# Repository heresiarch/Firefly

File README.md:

# Firefly
Own Dervivation of an electronic Firefly simulator with AVR Tiny based on a thread from http://www.mikrocontroller.net/topic/99803.  
This device is really nice to see and a perfect gift.  
I use Eclipse Kepler with avrdude and AVR Eclipse Plugin http://sourceforge.net/projects/avr-eclipse/
PCB Layout with Eagle is included.  
Variant 1 was not running stable after a couple of weeks.  
Variant 2 got an hardware watchdog circuit applied was running longer but also died after couple of months.  
Some people in the forum have the circuit running for years, but I could not dig out why mine was failing.  
The circuit will be powerd with an solar cell and 2 AAA NiMH akkus, and will dimm the leds like fireflies in darkness using different patterns.  
The original author of the SW is mentioned in the thread above.   
I will make a new PCB with gold plated battery clips, which is in my opinion the problem of the unstability.
Also I'm thinking of converting the project to an PIC24 using only C and get rid of the assembler stuff.

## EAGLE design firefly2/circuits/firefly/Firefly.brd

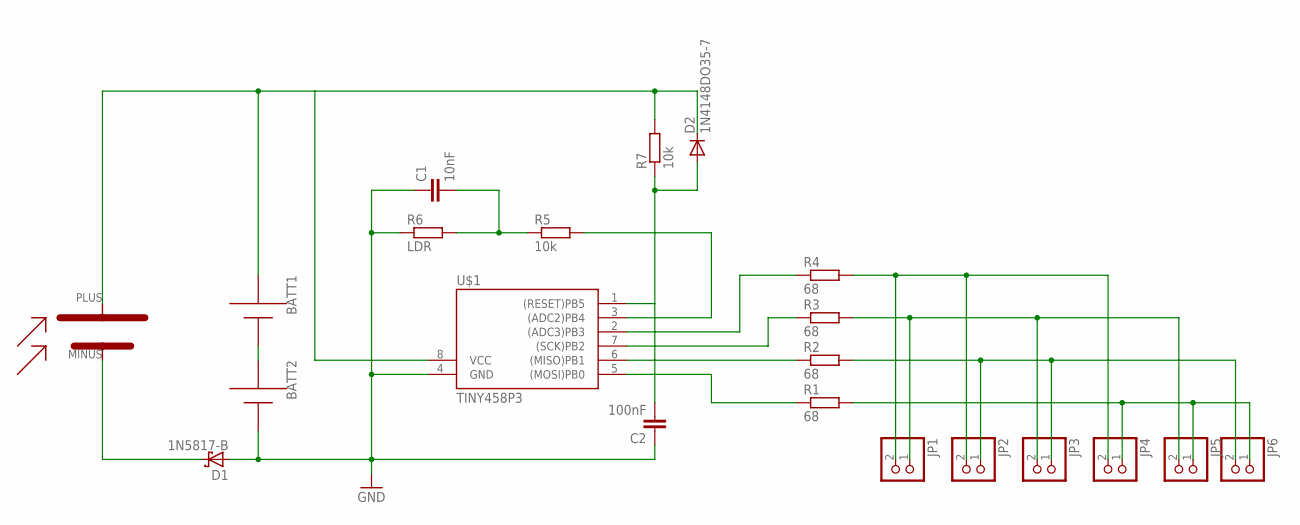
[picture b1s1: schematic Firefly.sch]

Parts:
BATT1, BATT2: AAA; 12BH412
C1: 10nF; C025-025X050
C2: 100nF; C075-032X103
D1: 1N5817-B; DO41-7.6
D2: 1N4148DO35-7; DO35-7
JP1, JP2, JP3, JP4, JP5, JP6: PINHD-1X2; 1X02
R1, R2, R3, R4: 68; 0204/7
R5: 10k; 0207/10
R6: LDR; 0204/7
R7: 10k; 0204/7
U$1: TINY458P3; DIL08
U$2: SOLARCELL4V35MACONRAD; SOLARCELL35X39

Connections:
GND: BATT2.-, C1.1, C2.1, D1.A, R6.1, U$1.4 (GND)
unnamed: R1.1, U$1.5 ((MOSI)PB0)
unnamed: R2.1, U$1.6 ((MISO)PB1)
unnamed: R3.1, U$1.7 ((SCK)PB2)
unnamed: R4.1, U$1.2 ((ADC3)PB3)
unnamed: JP1.2, JP2.2, JP4.2, R4.2
unnamed: BATT1.-, BATT2.+
unnamed: JP2.1, JP3.1, JP6.2, R2.2
unnamed: JP1.1, JP3.2, JP5.2, R3.2
unnamed: C2.2, D2.A, R7.1, U$1.1 ((RESET)PB5)
unnamed: JP4.1, JP5.1, JP6.1, R1.2
unnamed: BATT1.+, D2.C, R7.2, U$1.8 (VCC), U$2.PLUS
unnamed: D1.C, U$2.MINUS
unnamed: R5.2, U$1.3 ((ADC2)PB4)
unnamed: C1.2, R5.1, R6.2

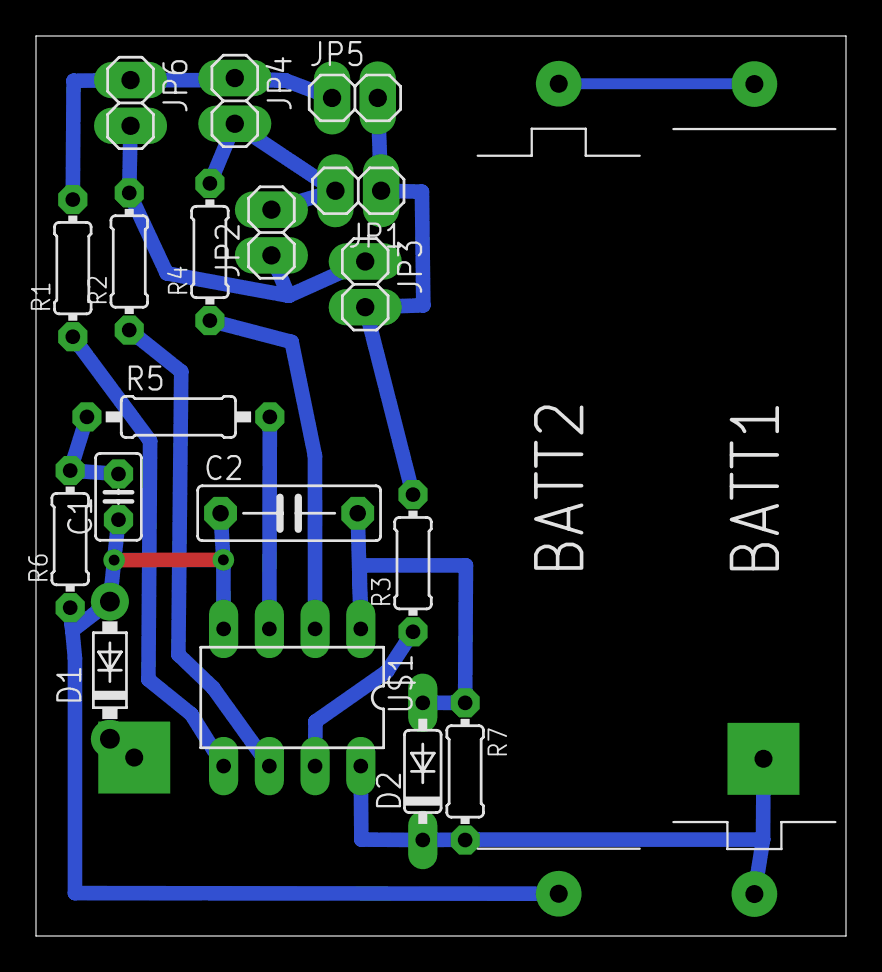
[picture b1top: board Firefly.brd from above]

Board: 2 copper layers, 45.0 x 50.0 mm, 21 parts (1 on the bottom side), 15 nets.

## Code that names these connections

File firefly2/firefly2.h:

#ifndef FIREFLY_H
#define FIREFLY_H

#include <inttypes.h>
#include <avr/eeprom.h>
#include <avr/pgmspace.h>
#include <util/delay.h>
#include "lfsr32.h"
#include "wave.h"

/*
   PB2 =      = InOut = LED0
   PB1 =      = InOut = LED1
   PB0 =      = InOut = LED2
   PB5 =      = InOut = LED3
   PB3 = ADC3 = Input = BAT+/SOLAR+
   PB4 = ADC2 = Input = SOLAR-

   connection schemata for LEDs are:
   - two antiparallel connected LEDs to two wire, makes six such wires
   - connect these wires to PB0-PB1, PB0-PB2, PB0-PB5, PB1-PB2, PB1-PB5, PB2-PB5
   - the order of these connections are not relevant

   setup:
   - install AVRootloader.HEX on AVR
   - setup fuses to XTAL=8Mhz, no Brownout Detection, no WDTON
   - connect RS232 on PB2 and test Bootloader (reading/writing EEPROM)
   - setup fuses to disable RESET Pin and lockbits
   - connect with bootloader an program FireFly.HEX
*/


#define FLAG_WAVE           (1 << 0)                    // PWM is active for a LED
#define FLAG_TIMER          (1 << 1)                    // PWM is active
#define FLAG_UPDATE         (1 << 2)                    // Watchdog signaled a update
#define FLAG_ISNIGHT        (1 << 3)                    // is at night
#define FLAG_MEASURE        (1 << 4)                    // measure battery and solarpanel

//#define MEASURE_INTERVAL    (uint16_t)(6 *  3750)       // each 6 minutes measure interval
//#define MEASURE_INTERVAL    (uint16_t)(2 *  3750)       // each 2 minutes measure interval
#define MEASURE_INTERVAL    (uint16_t)(1 *  375)       // each 2 * 6 seconds measure interval

#define BATTERY_OK          (uint16_t)(0.9 * 400)       // 0.9 Volt

// LED Rows, Pins connected to LEDs
#define R0  (1 << PB0)
#define R1  (1 << PB1)
#define R2  (1 << PB2)
#define R3  (1 << PB3)

// bitmasks for driving LEDs on PORTB and DDRB, first value are for PORTB (always 1),
// next 3 values for DDRB to connect LEDs to GND (on) or as high-Z input (off)
// you can reorder this array iff needed so long as each row depends to only one PORTB value,
// means in each row you can savely reorder the colums and/or you can savely reorder the rows.
const prog_uint8_t ddr_data[16] = {
    R0, R0^R1, R0^R2, R0^R3,
    R1, R1^R0, R1^R2, R1^R3,
    R2, R2^R0, R2^R1, R2^R3,
    R3, R3^R0, R3^R1, R3^R2};

// a Firefly
typedef struct {
    uint16_t wave_end;                              // pointer to end of wave samples
    uint16_t wave_ptr;                              // pointer to current wave sample == PWM Dutycylce of one LED
    uint16_t hungry;                                // energy points that must be feed to activate lightning of firefly
    uint16_t energy;                                // next energy points to add to hungry
} firefly_t;                                        // one energy/hungry point relates to one WDT cycle of 16ms

typedef firefly_t* firefly_p;

// some macros, don't use WinAVR GCC default macros because these produce inefficient compiled code
#define  wdt_reset()         asm volatile("wdr")
#define  cli()               asm volatile("cli")
#define  sei()               asm volatile("sei")
#define  sleep_cpu()         asm volatile("sleep")

// read word from FLASH with postincrement addresspointer
#define pgm_read_word_inc(addr) \
(__extension__({                \
    uint16_t __result;          \
    __asm__                     \
    (                           \
        "lpm %A0, Z+" "\n\t"    \
        "lpm %B0, Z+" "\n\t"    \
        : "=r" (__result),      \
          "=z" (addr)           \
        : "1" (addr)            \
    );                          \
    __result;                   \
}))


#endif

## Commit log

2015-02-06 hallo
